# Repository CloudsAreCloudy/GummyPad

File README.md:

# GummyPad
An ESP32 C3 SuperMini Macropad with 12 Keys, an OLED Display, Rotary Encoder, and RGB LEDs!

## Bill of Materials (BOM)
| Part | Price (USD) | Quantity | Where to find it |
| ---- | ----- | -------- | ---------------- |
| M3x4mmx4.2mm Heat Set Brass Inserts | 0.45$ | 10 | [Purchase Here](https://quartzcomponents.com/products/m3-x-4mm-brass-heat-set-threaded-round-insert-nut-10-pcs?variant=45107588169962) |
| 100nF Capacitors | 0.32$ | 9 | [Purchase Here](https://quartzcomponents.com/products/100nf-0-1uf-50v-capacitor-0805-smd-pack-of-20-piece?variant=43456389218538) |
| SSD1306 0.96 Inch OLED Display | 1.51$ | 1 | [Purchase Here](https://quartzcomponents.com/products/oled-display-0-96-inch-i2c-interface-4-pin-blue-ssd1306?variant=33049183060103) |
| 3.7V 2000mAH Li-Po Battery | 2.58$ | 1 | [Purchase Here](https://quartzcomponents.com/products/3-7v-2000mah-li-po-rechargeable-battery-523450?variant=44853322449130) |
| TP4056 Charging Module | 0.17$ | 1 | [Purchase Here](https://quartzcomponents.com/products/tp4056-battery-charging-protection-module-type-c?variant=39545849774264) |
| 1N148 High-speed Diode | 0.38$ | 12 | [Purchase Here](https://quartzcomponents.com/products/1n4148-zener-diode?variant=42817413546218) |
| KY-040 Rotary Encoder | 0.49$ | 1 | [Purchase Here](https://quartzcomponents.com/products/rotary-encoder-module-ky-040?variant=39545890963640) |
| WS2821B 5050 LED Light | 0.94$ | 9 | [Purchase Here](https://probots.co.in/ws2812b-rgb-led-chip-5050-smd-white-addressable-intelligent.html) |
| M3 x 6mm Screws | 0.13$ | 10 | [Purchase Here](https://onlyscrews.in/products/m3-x-6mm-phillips-csk-ss-304-screw-dia-3mm-length-6mm?variant=52107976802617)
| M2.5 x 4mm Screws | 0.03$ | 2 | [Purchase Here](https://onlyscrews.in/products/m2-5-x-4mm-phillips-csk-ss-304-screw-dia-2-5mm-length-4mm?variant=51156921123129) |
| Keyboard Switches | 1.57$ | 12 | [Purchase Here](https://meckeys.com/shop/accessories/keyboard-accessories/key-switches/regular-switch-3pin/?attribute_pa_key-switches=regular-black) |
| ESP32-C3 Super Mini | 2.86$ | 1 | [Purchase Here](https://quartzcomponents.com/products/esp32-c3-super-mini-development-board-with-soldered-headers-hw-466ab?variant=45727228887274)
| PCB from JLCPCB | 2.18$ | 5 (MOQ) | [Purchase Here](JLCPCB.com) |
| 3D Printing (Self) | 0$ | 1 | NA |
| Shipping | 2.83$ | NA | NA |
| **Total** | 16.44$ | | |

## How can I build it?
 **Required Libraries:**
- ADAFRUIT_SSD1306
- Adafruit BusIO
- Adafruit GFX Library
- Adafruit Neopixel
- Keypad by Mark Stanley and Alexander Brevig
- NimBLE-Arduino
- Rotary Encoder by Matthias Hertel

All you need to do is solder the Capacitors, Display, TP4056 Module, Battery, Diodes, Switches, Rotary Encoder, and LEDs onto the PCB, 3D Print the case and use a soldering iron to push the heat set inserts into place (M2.5 screws intentionally dont have heat set inserts), compile and upload the macropad.ino file onto the ESP32, and you should be good to go! By default the macropad uses F13-F24, which you can reprogram to do various things in your operating system of choice :D

## [Demo Video](https://youtu.be/8k5XH5p4000)

## Files more than 25MB
[Download F3D file here!](https://drive.google.com/file/d/1IniMza_yKS0Taz5GG_T-p-VxVlQoaIGq/view?usp=drive_link) <br>
[Download Assembled STEP file here!](https://drive.google.com/file/d/1E9eQrAUTnUo944QDMf3ixqt9oS76ekv8/view?usp=drive_link)
<br>
**------------------------------------------------**
<br>
<br>

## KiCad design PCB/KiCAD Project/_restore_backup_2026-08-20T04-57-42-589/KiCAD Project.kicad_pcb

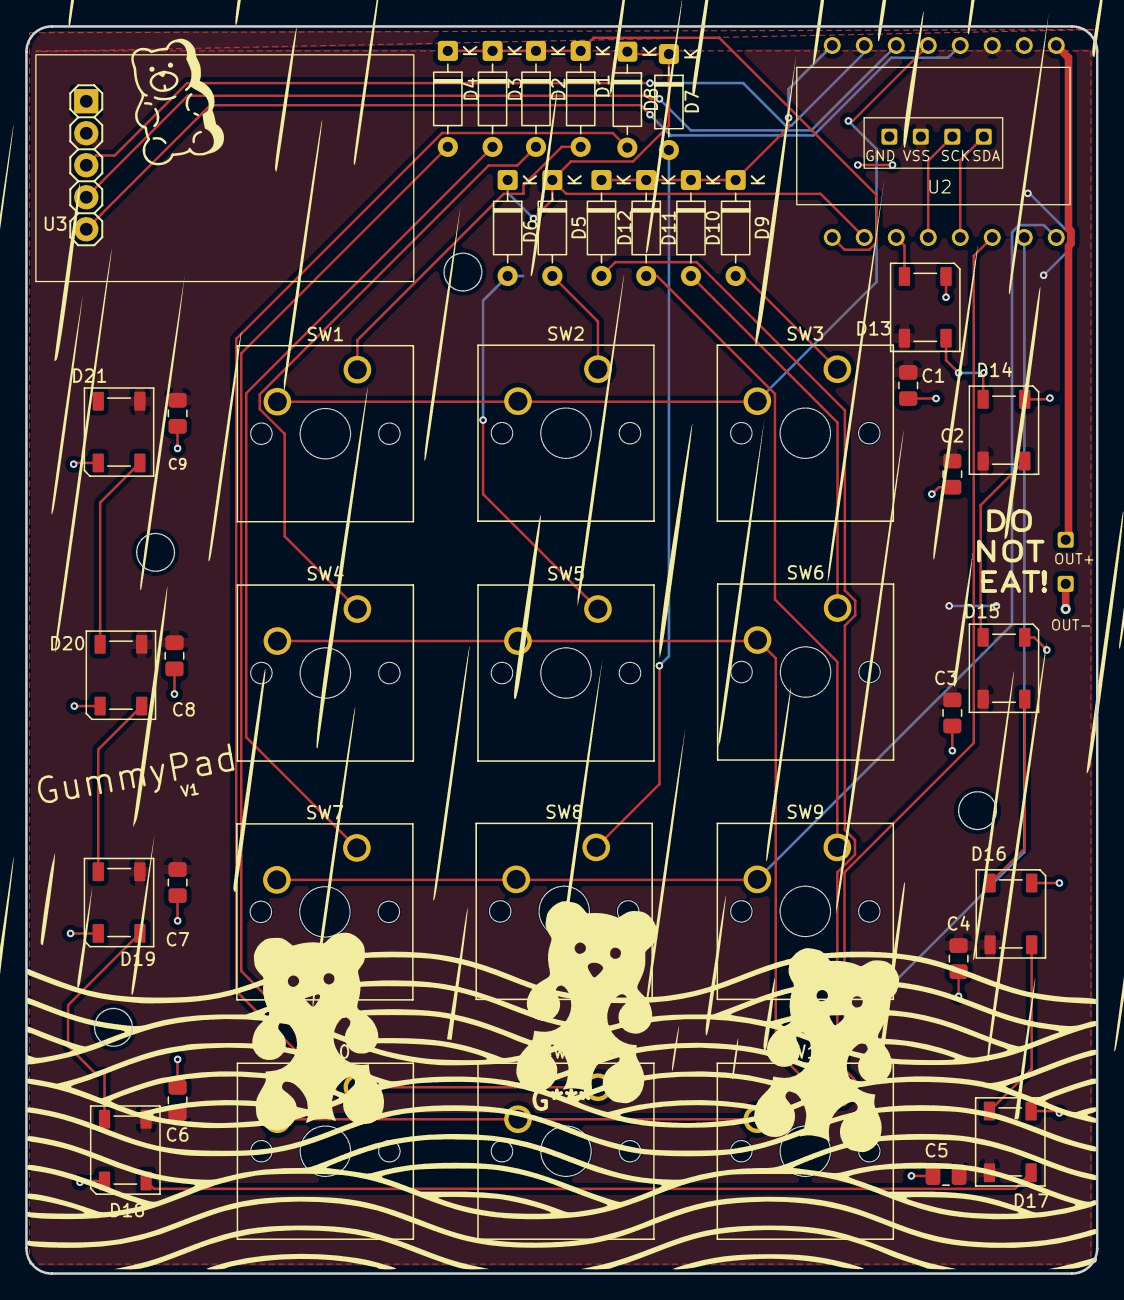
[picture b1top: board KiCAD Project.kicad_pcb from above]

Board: 2 copper layers, 85.0 x 99.0 mm, 46 parts (1 on the bottom side), 36 nets.

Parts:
C1, C2, C3, C4, C5, C6, C7, C8, C9: 100nF; C_0805_2012Metric_Pad1.18x1.45mm_HandSolder
D1, D2, D3, D4, D5, D6, D7, D8, D9, D10, D11, D12: D_DO-35_SOD27_P7.62mm_Horizontal
D13, D14, D15, D16, D17, D18, D19, D20, D21: WS2812B; LED_WS2812B_PLCC4_5.0x5.0mm_P3.2mm
SW1, SW2, SW3, SW4, SW5, SW6, SW7, SW8, SW9, SW10, SW11, SW12: SW_Cherry_MX_1.00u_PCB
TP1: TP4056 Basic
U1: ESP32-C3_SUPERMINI_TH; MODULE_ESP32-C3_SUPERMINI_TH
U2: ER_OLEDM0.91_1x-I2C; I2C Display
U3: KY-040; KY-040-PORT

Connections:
+3.3V: C1.1, C2.1, C3.1, C4.1, C5.1, C6.1, C7.1, C8.1, C9.1, D13.1 (VDD), D14.1 (VDD), D15.1 (VDD), D16.1 (VDD), D17.1 (VDD), D18.1 (VDD), D19.1 (VDD), D20.1 (VDD), D21.1 (VDD), U1.3.3 (3V3), U2.2 (VCC), U3.VCC
+5V: TP1.1 (OUT+), U1.5V
/Column 0: D1.1 (K), D2.1 (K), D3.1 (K), D4.1 (K), U1.21 (GPIO21)
/Column 1: D5.1 (K), D6.1 (K), D7.1 (K), D8.1 (K), U1.20 (GPIO20)
/Column 2: D9.1 (K), D10.1 (K), D11.1 (K), D12.1 (K), U1.0 (GPIO0)
/LED_Data: D13.4 (DIN), U1.10 (GPIO10)
/OLED_SCL: U1.9 (GPIO9), U2.3 (SCL)
/OLED_SDA: U1.8 (GPIO8), U2.4 (SDA)
/RotE_A: U1.4 (GPIO4), U3.CLK
/RotE_B: U1.2 (GPIO2), U3.DT
/RotE_Sw: U1.1 (GPIO1), U3.SW
/Row 0: SW1.2, SW2.2, SW3.2, U1.3 (GPIO3)
/Row 1: SW4.2, SW5.2, SW6.2, U1.7 (GPIO7)
/Row 2: SW7.2, SW8.2, SW9.2, U1.5 (GPIO5)
/Row 3: SW10.2, SW11.2, SW12.2, U1.6 (GPIO6)
GND: C1.2, C2.2, C3.2, C4.2, C5.2, C6.2, C7.2, C8.2, C9.2, D13.3 (VSS), D14.3 (VSS), D15.3 (VSS), D16.3 (VSS), D17.3 (VSS), D18.3 (VSS), D19.3 (VSS), D20.3 (VSS), D21.3 (VSS), TP1.4 (OUT-), U1.G (GND), U2.1 (GND), U3.GND
unnamed: D1.2 (A), SW1.1
unnamed: D2.2 (A), SW4.1
unnamed: D3.2 (A), SW7.1
unnamed: D4.2 (A), SW10.1
unnamed: D5.2 (A), SW2.1
unnamed: D6.2 (A), SW5.1
unnamed: D7.2 (A), SW8.1
unnamed: D8.2 (A), SW11.1
unnamed: D9.2 (A), SW3.1
unnamed: D10.2 (A), SW6.1
unnamed: D11.2 (A), SW9.1
unnamed: D12.2 (A), SW12.1
unnamed: D13.2 (DOUT), D14.4 (DIN)
unnamed: D14.2 (DOUT), D15.4 (DIN)
unnamed: D15.2 (DOUT), D16.4 (DIN)
unnamed: D16.2 (DOUT), D17.4 (DIN)
unnamed: D17.2 (DOUT), D18.4 (DIN)
unnamed: D18.2 (DOUT), D19.4 (DIN)
unnamed: D19.2 (DOUT), D20.4 (DIN)
unnamed: D20.2 (DOUT), D21.4 (DIN)
